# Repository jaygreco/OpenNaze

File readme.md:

In early 2016, I designed an all-in-one flight controller with the goals of having a tightly-integrated FC with integrated PDB and OSD system. I ended up completing it right around the same time many commercial FCs began including lots of the features I was looking for. I took it as far as the prototype phase, but didn't push it any further.

I recently came across the files and decided to open-source them; it was my goal all along and it seems like a waste to do so much (FUN) reverse-engineering and new design of hardware and firmware without sharing with others who may be interested. 

UPDATE: I've released the entire all-in-one design as well. You can find more info [here](http://jay-greco.com/openaio).

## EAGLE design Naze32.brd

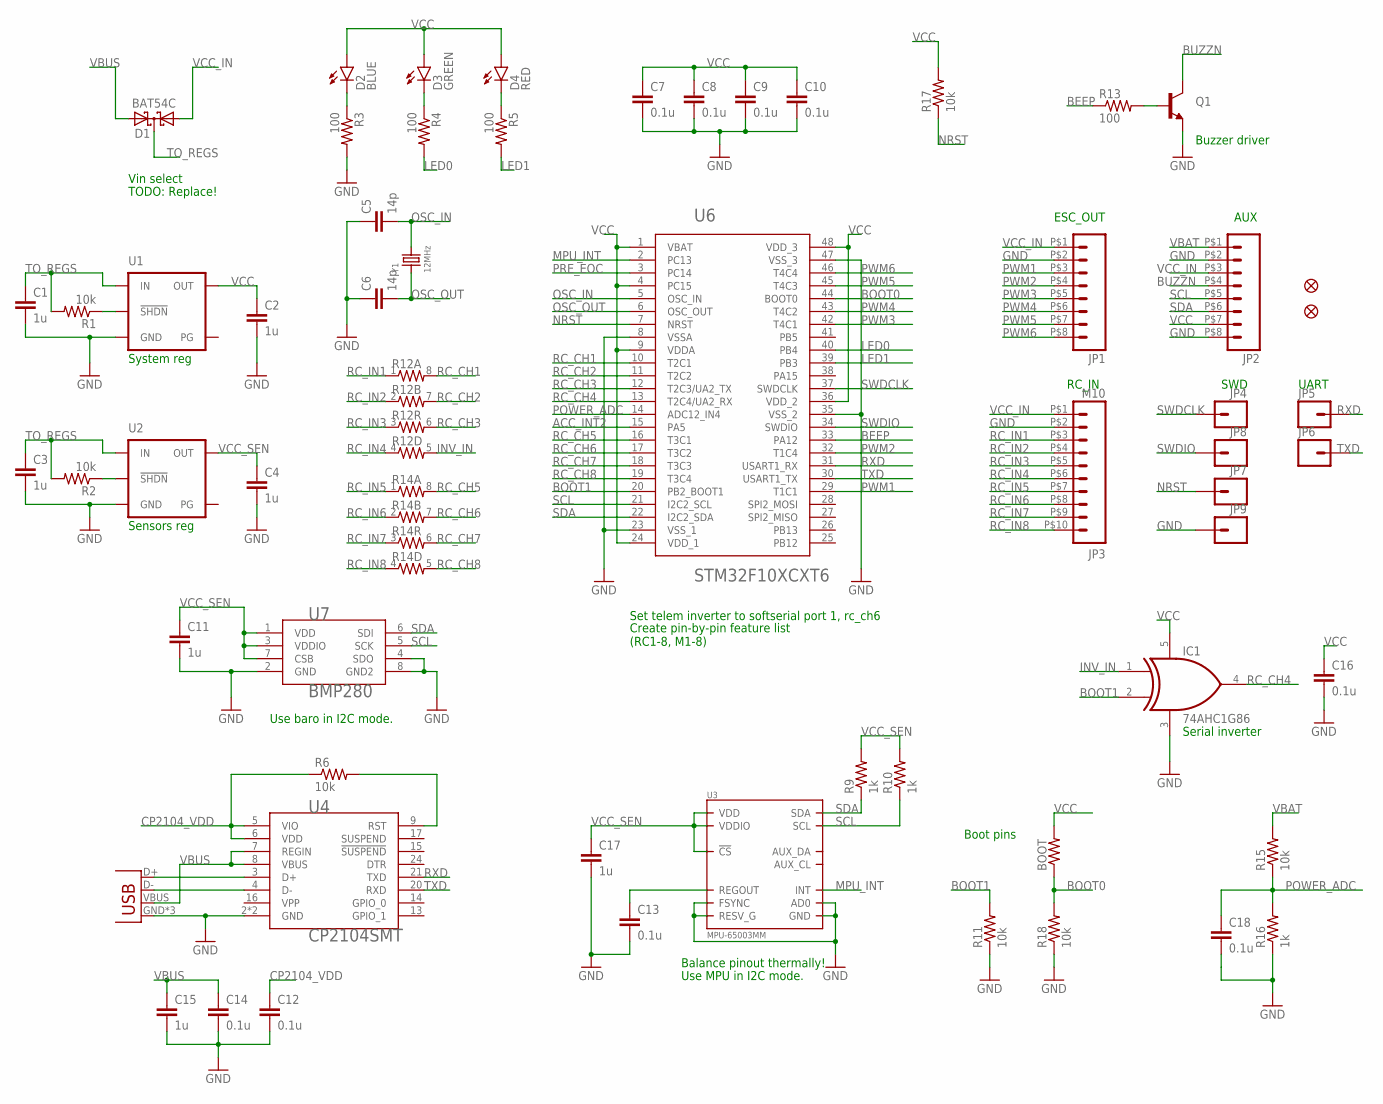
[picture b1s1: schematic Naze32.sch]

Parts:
BOOT: RESISTOR0603; 0603-RES
C1, C2, C3, C4, C11, C15, C17: 1u; 0402-CAP
C5, C6: 14p; 0402-CAP
C7, C8, C9, C10, C12, C13, C14, C16, C18: 0.1u; 0402-CAP
D1: BAT54C; SOT23
D2: BLUE; LED-0603
D3: GREEN; LED-0603
D4: RED; LED-0603
FID1, FID2: FIDUCIALUFIDUCIAL; MICRO-FIDUCIAL
IC1: 74AHC1G86; SC70-5
J1: USB-MICROB
JP1, JP2: M08PAD-1X8; PAD-1X8
JP3: M10; PAD_1X10
JP4: SCK; PAD-ROUND
JP5: RX; PAD-ROUND
JP6: TX; PAD-ROUND
JP7: RST; PAD-ROUND
JP8: IO; PAD-ROUND
JP9: GND; PAD-ROUND
Q1: TRANSISTOR_NPNSOT23; SOT23
R1, R2, R6, R11, R15, R17, R18: 10k; 0402-RES
R3, R4, R5, R13: 100; 0402-RES
R9, R10, R16: 1k; 0402-RES
R12, R14: RESISTOR-ARRAY0603-ARV; 0603-ARV
U1, U2: MCP18243.3V; SOT23-5
U3: MPU-65003MM; QFN-24_3X3
U4: CP2104SMT; QFN-24_ALT2
U6: STM32F10XCXT6; TQFP48
U7: BMP280; LGA8
Y1: 12MHz; 3.2X2.5MM

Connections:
ACC_INT2: U6.15 (PA5)
BEEP: R13.1, U6.33 (PA12)
BOOT0: BOOT.1, R18.2, U6.44 (BOOT0)
BOOT1: IC1.2 (I1), R11.2, U6.20 (PB2_BOOT1)
BUZZN: JP2.P$4 (4), Q1.3 (C)
CP2104_VDD: C12.1, R6.1, U4.5 (VIO), U4.6 (VDD)
GND: C1.2, C2.2, C3.2, C4.2, C5.1, C6.1, C7.2, C8.2, C9.2, C10.2, C11.2, C12.2, C13.2, C14.2, C15.2, C16.2, C17.2, C18.2, IC1.3 (GND), J1.GND, J1.MT1 (GND), J1.MT2 (GND), JP1.P$2 (2), JP2.P$2 (2), JP2.P$8 (8), JP3.P$2 (2), JP9.P$1, Q1.2 (E), R3.2, R11.1, R16.1, R18.1, U1.2 (GND), U2.2 (GND), U3.9 (AD0), U3.11 (FSYNC), U3.18 (GND), U3.20 (RESV_G), U4.2 (GND), U4.EP (GND), U6.8 (VSSA), U6.23 (VSS_1), U6.35 (VSS_2), U6.47 (VSS_3), U7.2 (GND), U7.4 (SDO), U7.8 (GND2)
INV_IN: IC1.1 (I0), R12.5 (2)
LED0: R4.2, U6.40 (PB4)
LED1: R5.2, U6.39 (PB3)
MPU_INT: U3.12 (INT), U6.2 (PC13)
unnamed: J1.D+, U4.3 (D+)
unnamed: R2.1, U2.3 (!SHDN)
unnamed: R1.1, U1.3 (!SHDN)
unnamed: D2.C, R3.1
unnamed: J1.D-, U4.4 (D-)
unnamed: D3.C, R4.1
unnamed: D4.C, R5.1
unnamed: R6.2, U4.9 (RST)
unnamed: C13.1, U3.10 (REGOUT)
unnamed: Q1.1 (B), R13.2
NRST: JP7.P$1, R17.1, U6.7 (NRST)
OSC_IN: C5.2, U6.5 (OSC_IN), Y1.3 (2)
OSC_OUT: C6.2, U6.6 (OSC_OUT), Y1.1
POWER_ADC: C18.1, R15.1, R16.2, U6.14 (ADC12_IN4)
PRE_EOC: U6.3 (PC14)
PWM1: JP1.P$3 (3), U6.29 (T1C1)
PWM2: JP1.P$4 (4), U6.32 (T1C4)
PWM3: JP1.P$5 (5), U6.42 (T4C1)
PWM4: JP1.P$6 (6), U6.43 (T4C2)
PWM5: JP1.P$7 (7), U6.45 (T4C3)
PWM6: JP1.P$8 (8), U6.46 (T4C4)
RC_CH1: R12.8 (2), U6.10 (T2C1)
RC_CH2: R12.7 (2), U6.11 (T2C2)
RC_CH3: R12.6 (2), U6.12 (T2C3/UA2_TX)
RC_CH4: IC1.4 (O), U6.13 (T2C4/UA2_RX)
RC_CH5: R14.8 (2), U6.16 (T3C1)
RC_CH6: R14.7 (2), U6.17 (T3C2)
RC_CH7: R14.6 (2), U6.18 (T3C3)
RC_CH8: R14.5 (2), U6.19 (T3C4)
RC_IN1: JP3.P$3 (3), R12.1
RC_IN2: JP3.P$4 (4), R12.2 (1)
RC_IN3: JP3.P$5 (5), R12.3 (1)
RC_IN4: JP3.P$6 (6), R12.4 (1)
RC_IN5: JP3.P$7 (7), R14.1
RC_IN6: JP3.P$8 (8), R14.2 (1)
RC_IN7: JP3.P$9 (9), R14.3 (1)
RC_IN8: JP3.P$10 (10), R14.4 (1)
RXD: JP5.P$1, U4.21 (TXD), U6.31 (USART1_RX)
SCL: JP2.P$5 (5), R10.1, U3.23 (SCL), U6.21 (I2C2_SCL), U7.5 (SCK)
SDA: JP2.P$6 (6), R9.1, U3.24 (SDA), U6.22 (I2C2_SDA), U7.6 (SDI)
SWDCLK: JP4.P$1, U6.37 (SWDCLK)
SWDIO: JP8.P$1, U6.34 (SWDIO)
TO_REGS: C1.1, C3.1, D1.3 (CC), R1.2, R2.2, U1.1 (IN), U2.1 (IN)
TXD: JP6.P$1, U4.20 (RXD), U6.30 (USART1_TX)
VBAT: JP2.P$1 (1), R15.2
VBUS: C14.1, C15.1, D1.2 (A2), J1.VBUS, U4.7 (REGIN), U4.8 (VBUS)
VCC: BOOT.2, C2.1, C7.1, C8.1, C9.1, C10.1, C16.1, D2.A, D3.A, D4.A, IC1.5 (VCC), JP2.P$7 (7), R17.2, U1.5 (OUT), U6.1 (VBAT), U6.4 (PC15), U6.9 (VDDA), U6.24 (VDD_1), U6.36 (VDD_2), U6.48 (VDD_3)
VCC_IN: D1.1 (A1), JP1.P$1 (1), JP2.P$3 (3), JP3.P$1 (1)
VCC_SEN: C4.1, C11.1, C17.1, R9.2, R10.2, U2.5 (OUT), U3.8 (VDDIO), U3.13 (VDD), U3.22 (!CS), U7.1 (VDD), U7.3 (VDDIO), U7.7 (CSB)

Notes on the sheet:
Use baro in I2C mode.
Use MPU in I2C mode.
Balance pinout thermally!
Sensors reg
System reg
Vin select
Serial inverter
Buzzer driver
Set telem inverter to softserial port 1, rc_ch6
SWD
UART
RC_IN
ESC_OUT
AUX
Boot pins
Create pin-by-pin feature list (RC1-8, M1-8)
TODO: Replace!

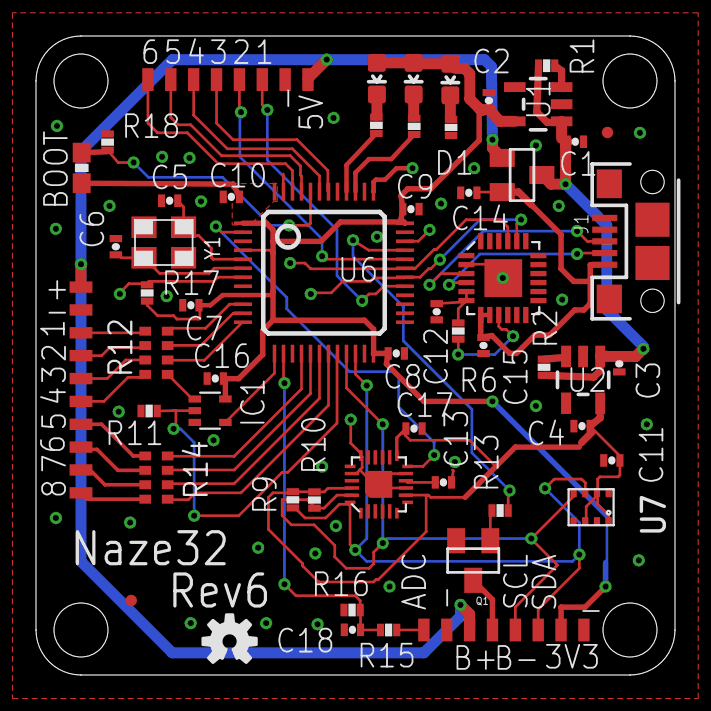
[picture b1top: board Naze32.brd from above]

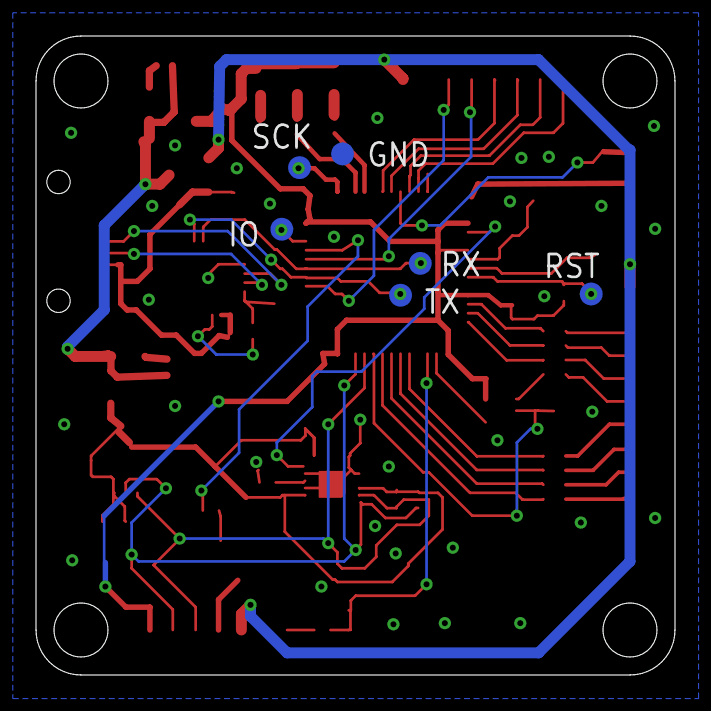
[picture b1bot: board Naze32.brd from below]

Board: 2 copper layers, 35.5 x 35.5 mm, 61 parts (6 on the bottom side), 58 nets.

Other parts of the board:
U$1: OSHW-LOGO-S

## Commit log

2018-03-28 Uploaded complete Naze routing
    Uploaded a downrev'd version previously. Updated to the compete version.

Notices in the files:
parts and their libraries:
SparkFun-Aesthetics: Licensing: Creative Commons ShareAlike 4.0 International - https://creativecommons.org/licenses/by-sa/4.0
